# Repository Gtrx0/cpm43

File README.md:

# CPM43
40% Mechanical keyboard PCB

# [Layout](http://www.keyboard-layout-editor.com/#/gists/e3d0a9a1f7fb6537a82bb3f0c82ddf35)

## Features
* In-switch LED support.
* Individually addressible RGB underglow provided by 14 separate WS2812B LEDs.
* USB Type-C connector on the left side.
* Compatible with Cherry MX and ALPS switches. 
* Integrated 16MHz Atmega32u4 microcontroller for better QMK compatibility.
* USB ESD protection circuit.
* ICSP programming header just in case you try something a bit too extreme and need to unbrick it.
* 0805 SMD and through hole Diode/resistor compatibility for ease of assembly.
* USB breakout for extra redundency.

## Warning
KiCad 5 or above is needed to open this project. KiCad 4 or below won't work.

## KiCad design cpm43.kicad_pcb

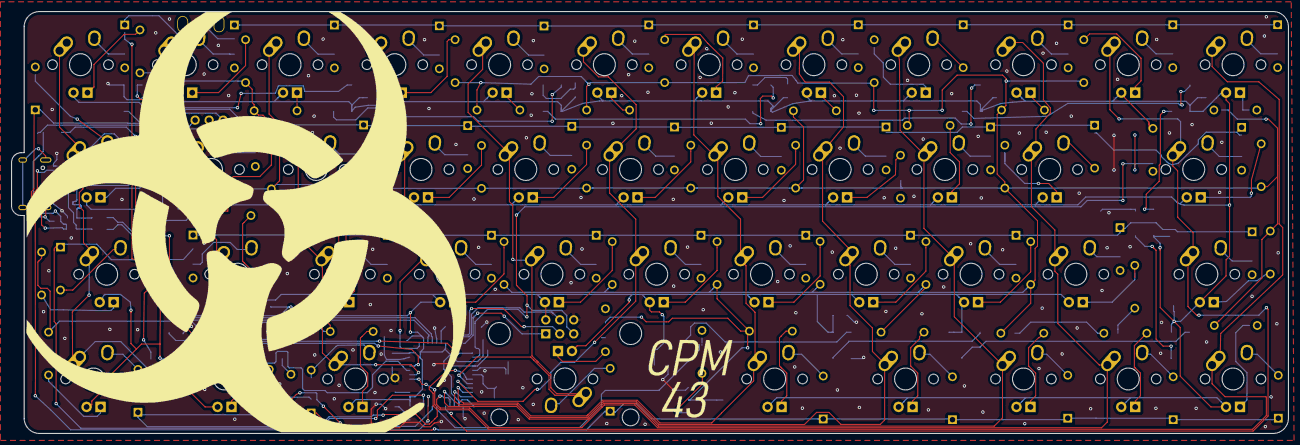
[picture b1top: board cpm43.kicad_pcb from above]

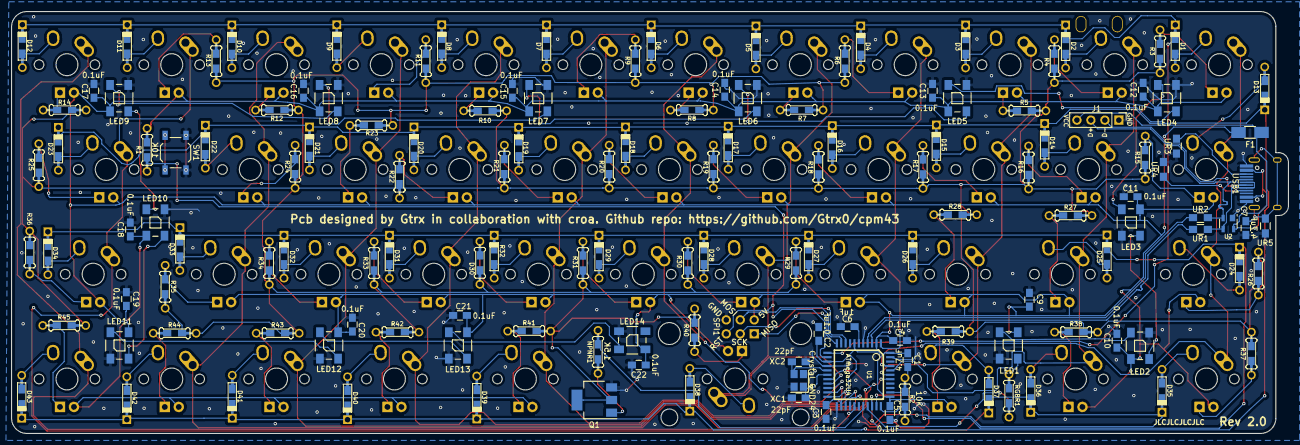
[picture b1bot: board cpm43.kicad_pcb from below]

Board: 2 copper layers, 232.2 x 76.7 mm, 186 parts (50 on the bottom side), 138 nets.

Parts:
C1: 0.1uf; C_0805_HandSoldering
C2, C3, C5, C9, C10, C11, C12, C13, C14, C15, C16, C17, C18, C19, C20, C21, C22: 0.1uF; C_0805_HandSoldering
C4, C7: 4.7uF; C_0805_HandSoldering
C6: 1uF; C_0805_HandSoldering
D1, D2, D3, D4, D5, D6, D7, D8, D9, D10, D11, D12, D13, D14, D15, D16, D17, D18, D19, D20, D21, D22, D23, D24, D25, D26, D27, D28, D29, D30, D31, D32, D33, D34, D35, D36, D37, D38, D39, D40, D41, D42, D43: D; Diode-Hybrid-Back
F1: 500mA Hold; Fuse_SMD1206_HandSoldering
J1: Conn_01x04; Pin_Header_Straight_1x04_Pitch2.54mm
LED1, LED2, LED3, LED4, LED5, LED6, LED7, LED8, LED9, LED10, LED11, LED12, LED13, LED14: WS2812B
MX1, MX2, MX3, MX4, MX5, MX6, MX7, MX8, MX9, MX10, MX11, MX12, MX14, MX15, MX16, MX17, MX18, MX19, MX20, MX21, MX22, MX25, MX26, MX27, MX28, MX29, MX30, MX31, MX32, MX33, MX41, MX42, MX43: MX-1U
MX13: MX-1.25U; MX-1.25U-FLIPPED
MX23: MX-1.75U
MX24: MX-1.5U
MX34: MX-1.25U; MX-1.5U
MX35, MX36, MX37, MX39, MX40: MX-1.25U
MX38: MX-2.75U
NPNR1: 1.5k; Resistor-Hybrid-Back
P?: CONN_1; PIN_1
P?#2: CONN_1; PIN_1
Q1: Q_NPN_BCE; SOT-223-3_TabPin2
R1, R2: 10k; Resistor-Hybrid-Back
R3, R4, R5, R6, R7, R8, R9, R10, R11, R12, R13, R14, R15, R16, R17, R18, R19, R20, R21, R22, R23, R24, R25, R26, R27, R28, R29, R30, R31, R32, R33, R34, R35, R36, R37, R38, R39, R40, R41, R42, R43, R44, R45: 470; Resistor-Hybrid-Back
RGBR1: 470; Resistor-Hybrid-Back
SPI1: 2x3 SPI; Pin_Header_Straight_2x03_Pitch2.54mm
SW1: SW_PUSH; SW_SPST_TL3342
U1: ATmega32U4; QFP44
U2: PRTR5V0U2X; SOT143B
UR1, UR2: 22; R_0805_HandSoldering
UR3, UR4: 5.1k; R_0805_HandSoldering
UR5: 1M; R_0805_HandSoldering
USB1: HRO-TYPE-C-31-M-12; HRO-TYPE-C-31-M-12-HandSoldering
X1: Crystal_GND24; Crystal_SMD_3225-4pin_3.2x2.5mm
XC1, XC2: 22pF; C_0805_HandSoldering

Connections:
+5V: C1.1, C2.1, C3.1, C4.1, C5.1, C9.1, C10.1, C11.1, C12.1, C13.1, C14.1, C15.1, C16.1, C17.1, C18.1, C19.1, C20.1, C21.1, C22.1, F1.2, LED1.1, LED2.1, LED3.1, LED4.1, LED5.1, LED6.1, LED7.1, LED8.1, LED9.1, LED10.1, LED11.1, LED12.1, LED13.1, LED14.1, MX1.3, MX2.3, MX3.3, MX4.3, MX5.3, MX6.3, MX7.3, MX8.3, MX9.3, MX10.3, MX11.3, MX12.3, MX13.3, MX14.3, MX15.3, MX16.3, MX17.3, MX18.3, MX19.3, MX20.3, MX21.3, MX22.3, MX23.3, MX24.3, MX25.3, MX26.3, MX27.3, MX28.3, MX29.3, MX30.3, MX31.3, MX32.3, MX33.3, MX34.3, MX35.3, MX36.3, MX37.3, MX38.3, MX39.3, MX40.3, MX41.3, MX42.3, MX43.3, R1.1, SPI1.2, U1.2, U1.7, U1.14, U1.24, U1.34, U1.44
COL0: MX1.1, MX13.1, MX24.1, MX35.1, U1.41
COL1: MX2.1, MX14.1, MX25.1, MX36.1, U1.40
COL2: MX3.1, MX15.1, MX26.1, MX37.1, U1.39
COL3: MX4.1, MX16.1, MX27.1, U1.1
COL4: MX5.1, MX17.1, MX28.1, MX38.1, U1.19
COL5: MX6.1, MX18.1, MX29.1, U1.20
COL6: MX7.1, MX19.1, MX30.1, MX39.1, U1.21
COL7: MX8.1, MX20.1, MX31.1, MX40.1, U1.22
COL8: MX9.1, MX21.1, MX32.1, MX41.1, U1.25
COL9: MX10.1, MX22.1, MX33.1, MX42.1, U1.26
COL10: MX11.1, MX23.1, MX34.1, U1.27
COL11: MX12.1, MX43.1, U1.38
D+: U1.4, UR2.1
D-: U1.3, UR1.2
GND: C1.2, C2.2, C3.2, C4.2, C5.2, C6.1, C7.1, C9.2, C10.2, C11.2, C12.2, C13.2, C14.2, C15.2, C16.2, C17.2, C18.2, C19.2, C20.2, C21.2, C22.2, J1.1, LED1.3, LED2.3, LED3.3, LED4.3, LED5.3, LED6.3, LED7.3, LED8.3, LED9.3, LED10.3, LED11.3, LED12.3, LED13.3, LED14.3, Q1.3, R2.2, SPI1.6, SW1.1, U1.5, U1.15, U1.23, U1.35, U1.43, U2.1, UR3.1, UR4.2, UR5.1, USB1.1, USB1.12, X1.2, XC1.2, XC2.2
LEDGND: Q1.2, R3.1, R4.1, R5.1, R6.1, R7.1, R8.1, R9.1, R10.1, R11.1, R12.1, R13.1, R14.1, R15.1, R16.1, R17.1, R18.1, R19.1, R20.1, R21.1, R22.1, R23.1, R24.1, R25.1, R26.1, R27.1, R28.1, R29.1, R30.1, R31.1, R32.1, R33.1, R34.1, R35.1, R36.1, R37.1, R38.1, R39.1, R40.1, R41.1, R42.1, R43.1, R44.1, R45.1
LEDPWM: NPNR1.1, U1.29
MISO: SPI1.1, U1.11
MOSI: SPI1.4, U1.10
unnamed: C6.2, U1.6
unnamed: C7.2, UR5.2, USB1.13
unnamed: D1.2, MX1.2
unnamed: D2.2, MX2.2
unnamed: D3.2, MX3.2
unnamed: D4.2, MX4.2
unnamed: D5.2, MX5.2
unnamed: D6.2, MX6.2
unnamed: D7.2, MX7.2
unnamed: D8.2, MX8.2
unnamed: D9.2, MX9.2
unnamed: D10.2, MX10.2
unnamed: D11.2, MX11.2
unnamed: D12.2, MX12.2
unnamed: D13.2, MX13.2
unnamed: D14.2, MX14.2
unnamed: D15.2, MX15.2
unnamed: D16.2, MX16.2
unnamed: D17.2, MX17.2
unnamed: D18.2, MX18.2
unnamed: D19.2, MX19.2
unnamed: D20.2, MX20.2
unnamed: D21.2, MX21.2
unnamed: D22.2, MX22.2
unnamed: D23.2, MX23.2
unnamed: D24.2, MX24.2
unnamed: D25.2, MX25.2
unnamed: D26.2, MX26.2
unnamed: D27.2, MX27.2
unnamed: D28.2, MX28.2
unnamed: D29.2, MX29.2
unnamed: D30.2, MX30.2
unnamed: D31.2, MX31.2
unnamed: D32.2, MX32.2
unnamed: D33.2, MX33.2
unnamed: D34.2, MX34.2
unnamed: D35.2, MX35.2
unnamed: D36.2, MX36.2
unnamed: D37.2, MX37.2
unnamed: D38.2, MX38.2
unnamed: D39.2, MX39.2
unnamed: D40.2, MX40.2
unnamed: D41.2, MX41.2
unnamed: D42.2, MX42.2
unnamed: D43.2, MX43.2
unnamed: J1.2, U2.3, UR1.1, USB1.5, USB1.7
unnamed: J1.3, U2.2, UR2.2, USB1.6, USB1.8
unnamed: LED1.2, LED2.4
unnamed: LED1.4, RGBR1.2
unnamed: LED2.2, LED3.4
unnamed: LED3.2, LED4.4
unnamed: LED4.2, LED5.4
unnamed: LED5.2, LED6.4
unnamed: LED6.2, LED7.4
unnamed: LED7.2, LED8.4
unnamed: LED8.2, LED9.4
unnamed: LED10.2, LED11.4
unnamed: LED9.2, LED10.4
unnamed: LED11.2, LED12.4
unnamed: LED12.2, LED13.4
unnamed: LED13.2, LED14.4
unnamed: MX1.4, R3.2
unnamed: MX2.4, R4.2
unnamed: MX3.4, R5.2
unnamed: MX4.4, R6.2
unnamed: MX5.4, R7.2
unnamed: MX6.4, R8.2
unnamed: MX7.4, R9.2
unnamed: MX8.4, R10.2
unnamed: MX9.4, R11.2
unnamed: MX10.4, R12.2
unnamed: MX11.4, R13.2
unnamed: MX12.4, R14.2
unnamed: MX13.4, R15.2
unnamed: MX14.4, R16.2
unnamed: MX15.4, R17.2
unnamed: MX16.4, R18.2
unnamed: MX17.4, R19.2
unnamed: MX18.4, R20.2
unnamed: MX19.4, R21.2
unnamed: MX20.4, R22.2
unnamed: MX21.4, R23.2
unnamed: MX22.4, R24.2
unnamed: MX23.4, R25.2
unnamed: MX24.4, R26.2
unnamed: MX25.4, R27.2
unnamed: MX26.4, R28.2
unnamed: MX27.4, R29.2
unnamed: MX28.4, R30.2
unnamed: MX29.4, R31.2
unnamed: MX30.4, R32.2
unnamed: MX31.4, R33.2
unnamed: MX32.4, R34.2
unnamed: MX33.4, R35.2
unnamed: MX34.4, R36.2
unnamed: MX35.4, R37.2
unnamed: MX36.4, R38.2
unnamed: MX37.4, R39.2
unnamed: MX38.4, R40.2
unnamed: MX39.4, R41.2
unnamed: MX40.4, R42.2
unnamed: MX41.4, R43.2
unnamed: MX42.4, R44.2
unnamed: MX43.4, R45.2
unnamed: NPNR1.2, Q1.1
unnamed: R2.1, U1.33
unnamed: U1.16, X1.3, XC2.1
unnamed: U1.17, X1.1, XC1.1
unnamed: UR3.2, USB1.10
unnamed: UR4.1, USB1.4
RGBIN: RGBR1.1, U1.30
ROW0: D1.1, D2.1, D3.1, D4.1, D5.1, D6.1, D7.1, D8.1, D9.1, D10.1, D11.1, D12.1, U1.12
ROW1: D13.1, D14.1, D15.1, D16.1, D17.1, D18.1, D19.1, D20.1, D21.1, D22.1, D23.1, U1.31
ROW2: D24.1, D25.1, D26.1, D27.1, D28.1, D29.1, D30.1, D31.1, D32.1, D33.1, D34.1, U1.32
ROW3: D35.1, D36.1, D37.1, D38.1, D39.1, D40.1, D41.1, D42.1, D43.1, U1.18
RST: R1.2, SPI1.5, SW1.2, U1.13
SCK: SPI1.3, U1.9
VCC: F1.1, J1.4, U2.4, USB1.2, USB1.11

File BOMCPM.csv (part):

"Source:","C:\Users\Gtrx\Desktop\40%\cpm43.sch"
"Date:","7/16/2018 1:50:26 AM"
"Tool:","Eeschema (6.0.0-rc1-dev)"
"Generator:","C:\Program Files\KiCad\bin\scripting\plugins/bom_csv_grouped_by_value.py"
"Component Count:","186"

"Individual Components:"

"Item","Qty","Reference(s)","Value","LibPart","Footprint","Datasheet"
"","","C1","0.1uF","device:C_Small","Capacitors_SMD:C_0805_HandSoldering",""
"","","C2","0.1uF","device:C_Small","Capacitors_SMD:C_0805_HandSoldering",""
"","","C3","0.1uF","device:C_Small","Capacitors_SMD:C_0805_HandSoldering",""
"","","C4","4.7uF","device:C_Small","Capacitors_SMD:C_0805_HandSoldering",""
"","","C5","0.1uF","device:C_Small","Capacitors_SMD:C_0805_HandSoldering",""
"","","C6","1uF","device:C_Small","Capacitors_SMD:C_0805_HandSoldering",""
"","","C7","4.7uF","device:C_Small","Capacitors_SMD:C_0805_HandSoldering",""
"","","C8","0.1uF","device:C_Small","Capacitors_SMD:C_0805_HandSoldering",""
"","","C9","0.1uF","device:C_Small","Capacitors_SMD:C_0805_HandSoldering",""
"","","C10","0.1uF","device:C_Small","Capacitors_SMD:C_0805_HandSoldering",""
"","","C11","0.1uF","device:C_Small","Capacitors_SMD:C_0805_HandSoldering",""
"","","C12","0.1uF","device:C_Small","Capacitors_SMD:C_0805_HandSoldering",""
"","","C13","0.1uF","device:C_Small","Capacitors_SMD:C_0805_HandSoldering",""
"","","C14","0.1uF","device:C_Small","Capacitors_SMD:C_0805_HandSoldering",""
"","","C15","0.1uF","device:C_Small","Capacitors_SMD:C_0805_HandSoldering",""
"","","C16","0.1uF","device:C_Small","Capacitors_SMD:C_0805_HandSoldering",""
"","","C17","0.1uF","device:C_Small","Capacitors_SMD:C_0805_HandSoldering",""
"","","C18","0.1uF","device:C_Small","Capacitors_SMD:C_0805_HandSoldering",""
"","","C19","0.1uF","device:C_Small","Capacitors_SMD:C_0805_HandSoldering",""
"","","C20","0.1uF","device:C_Small","Capacitors_SMD:C_0805_HandSoldering",""
"","","C21","0.1uF","device:C_Small","Capacitors_SMD:C_0805_HandSoldering",""
"","","C22","0.1uF","device:C_Small","Capacitors_SMD:C_0805_HandSoldering",""
"","","C23","0.1uF","device:C_Small","Capacitors_SMD:C_0805_HandSoldering",""
"","","D1","D","device:D_ALT","Keebio-Parts:Diode-Hybrid-Back",""
"","","D2","D","device:D_ALT","Keebio-Parts:Diode-Hybrid-Back",""
"","","D3","D","device:D_ALT","Keebio-Parts:Diode-Hybrid-Back",""
"","","D4","D","device:D_ALT","Keebio-Parts:Diode-Hybrid-Back",""
"","","D5","D","device:D_ALT","Keebio-Parts:Diode-Hybrid-Back",""
"","","D6","D","device:D_ALT","Keebio-Parts:Diode-Hybrid-Back",""
"","","D7","D","device:D_ALT","Keebio-Parts:Diode-Hybrid-Back",""
"","","D8","D","device:D_ALT","Keebio-Parts:Diode-Hybrid-Back",""
"","","D9","D","device:D_ALT","Keebio-Parts:Diode-Hybrid-Back",""
"","","D10","D","device:D_ALT","Keebio-Parts:Diode-Hybrid-Back",""
"","","D11","D","device:D_ALT","Keebio-Parts:Diode-Hybrid-Back",""
"","","D12","D","device:D_ALT","Keebio-Parts:Diode-Hybrid-Back",""
"","","D13","D","device:D_ALT","Keebio-Parts:Diode-Hybrid-Back",""
"","","D14","D","device:D_ALT","Keebio-Parts:Diode-Hybrid-Back",""
"","","D15","D","device:D_ALT","Keebio-Parts:Diode-Hybrid-Back",""
"","","D16","D","device:D_ALT","Keebio-Parts:Diode-Hybrid-Back",""
"","","D17","D","device:D_ALT","Keebio-Parts:Diode-Hybrid-Back",""
"","","D18","D","device:D_ALT","Keebio-Parts:Diode-Hybrid-Back",""
"","","D19","D","device:D_ALT","Keebio-Parts:Diode-Hybrid-Back",""
"","","D20","D","device:D_ALT","Keebio-Parts:Diode-Hybrid-Back",""
"","","D21","D","device:D_ALT","Keebio-Parts:Diode-Hybrid-Back",""
"","","D22","D","device:D_ALT","Keebio-Parts:Diode-Hybrid-Back",""
"","","D23","D","device:D_ALT","Keebio-Parts:Diode-Hybrid-Back",""
"","","D24","D","device:D_ALT","Keebio-Parts:Diode-Hybrid-Back",""
"","","D25","D","device:D_ALT","Keebio-Parts:Diode-Hybrid-Back",""
"","","D26","D","device:D_ALT","Keebio-Parts:Diode-Hybrid-Back",""
"","","D27","D","device:D_ALT","Keebio-Parts:Diode-Hybrid-Back",""
"","","D28","D","device:D_ALT","Keebio-Parts:Diode-Hybrid-Back",""
"","","D29","D","device:D_ALT","Keebio-Parts:Diode-Hybrid-Back",""
"","","D30","D","device:D_ALT","Keebio-Parts:Diode-Hybrid-Back",""
"","","D31","D","device:D_ALT","Keebio-Parts:Diode-Hybrid-Back",""
"","","D32","D","device:D_ALT","Keebio-Parts:Diode-Hybrid-Back",""
"","","D33","D","device:D_ALT","Keebio-Parts:Diode-Hybrid-Back",""
"","","D34","D","device:D_ALT","Keebio-Parts:Diode-Hybrid-Back",""
"","","D35","D","device:D_ALT","Keebio-Parts:Diode-Hybrid-Back",""
"","","D36","D","device:D_ALT","Keebio-Parts:Diode-Hybrid-Back",""
"","","D37","D","device:D_ALT","Keebio-Parts:Diode-Hybrid-Back",""
"","","D38","D","device:D_ALT","Keebio-Parts:Diode-Hybrid-Back",""
"","","D39","D","device:D_ALT","Keebio-Parts:Diode-Hybrid-Back",""
"","","D40","D","device:D_ALT","Keebio-Parts:Diode-Hybrid-Back",""
"","","D41","D","device:D_ALT","Keebio-Parts:Diode-Hybrid-Back",""
"","","D42","D","device:D_ALT","Keebio-Parts:Diode-Hybrid-Back",""
"","","D43","D","device:D_ALT","Keebio-Parts:Diode-Hybrid-Back",""
"","","F1","500mA Hold","device:Polyfuse_Small","Keebio-Parts:Diode-Hybrid-Back",""
"","","LED1","WS2812B","ws2812b:WS2812B","WS2812B:WS2812B",""
"","","LED2","WS2812B","ws2812b:WS2812B","WS2812B:WS2812B",""
"","","LED3","WS2812B","ws2812b:WS2812B","WS2812B:WS2812B",""
"","","LED4","WS2812B","ws2812b:WS2812B","WS2812B:WS2812B",""
"","","LED5","WS2812B","ws2812b:WS2812B","WS2812B:WS2812B",""
"","","LED6","WS2812B","ws2812b:WS2812B","WS2812B:WS2812B",""
"","","LED7","WS2812B","ws2812b:WS2812B","WS2812B:WS2812B",""
"","","LED8","WS2812B","ws2812b:WS2812B","WS2812B:WS2812B",""
"","","LED9","WS2812B","ws2812b:WS2812B","WS2812B:WS2812B",""
"","","LED10","WS2812B","ws2812b:WS2812B","WS2812B:WS2812B",""
"","","LED11","WS2812B","ws2812b:WS2812B","WS2812B:WS2812B",""
"","","LED12","WS2812B","ws2812b:WS2812B","WS2812B:WS2812B",""
"","","LED13","WS2812B","ws2812b:WS2812B","WS2812B:WS2812B",""
"","","LED14","WS2812B","ws2812b:WS2812B","WS2812B:WS2812B",""
"","","LED15","WS2812B","ws2812b:WS2812B","WS2812B:WS2812B",""
"","","MX1","MX-1U","MX_Alps_Hybrids:MX-1U","MX_Alps_Hybrid:MX-1U-NoLED",""
"","","MX2","MX-1U","MX_Alps_Hybrids:MX-1U","MX_Alps_Hybrid:MX-1U-NoLED",""
"","","MX3","MX-1U","MX_Alps_Hybrids:MX-1U","MX_Alps_Hybrid:MX-1U-NoLED",""
"","","MX4","MX-1U","MX_Alps_Hybrids:MX-1U","MX_Alps_Hybrid:MX-1U-NoLED",""
"","","MX5","MX-1U","MX_Alps_Hybrids:MX-1U","MX_Alps_Hybrid:MX-1U-NoLED",""
"","","MX6","MX-1U","MX_Alps_Hybrids:MX-1U","MX_Alps_Hybrid:MX-1U-NoLED",""
"","","MX7","MX-1U","MX_Alps_Hybrids:MX-1U","MX_Alps_Hybrid:MX-1U-NoLED",""
"","","MX8","MX-1U","MX_Alps_Hybrids:MX-1U","MX_Alps_Hybrid:MX-1U-NoLED",""
"","","MX9","MX-1U","MX_Alps_Hybrids:MX-1U","MX_Alps_Hybrid:MX-1U-NoLED",""
"","","MX10","MX-1U","MX_Alps_Hybrids:MX-1U","MX_Alps_Hybrid:MX-1U-NoLED",""
"","","MX11","MX-1U","MX_Alps_Hybrids:MX-1U","MX_Alps_Hybrid:MX-1U-NoLED",""
"","","MX12","MX-1U","MX_Alps_Hybrids:MX-1U","MX_Alps_Hybrid:MX-1U-NoLED",""
"","","MX13","MX-1.25U","MX_Alps_Hybrids:MX-1.25U","MX_Alps_Hybrid:MX-1.25U",""
"","","MX14","MX-1U","MX_Alps_Hybrids:MX-1U","MX_Alps_Hybrid:MX-1U",""
"","","MX15","MX-1U","MX_Alps_Hybrids:MX-1U","MX_Alps_Hybrid:MX-1U",""
"","","MX16","MX-1U","MX_Alps_Hybrids:MX-1U","MX_Alps_Hybrid:MX-1U",""
"","","MX17","MX-1U","MX_Alps_Hybrids:MX-1U","MX_Alps_Hybrid:MX-1U",""
"","","MX18","MX-1U","MX_Alps_Hybrids:MX-1U","MX_Alps_Hybrid:MX-1U",""
"","","MX19","MX-1U","MX_Alps_Hybrids:MX-1U","MX_Alps_Hybrid:MX-1U",""
"","","MX20","MX-1U","MX_Alps_Hybrids:MX-1U","MX_Alps_Hybrid:MX-1U",""
"","","MX21","MX-1U","MX_Alps_Hybrids:MX-1U","MX_Alps_Hybrid:MX-1U",""
"","","MX22","MX-1U","MX_Alps_Hybrids:MX-1U","MX_Alps_Hybrid:MX-1U",""
"","","MX23","MX-1.75U","MX_Alps_Hybrids:MX-1.75U","MX_Alps_Hybrid:MX-1.75U",""
"","","MX24","MX-1.5U","MX_Alps_Hybrids:MX-1.5U","MX_Alps_Hybrid:MX-1.5U",""
"","","MX25","MX-1U","MX_Alps_Hybrids:MX-1U","MX_Alps_Hybrid:MX-1U",""
"","","MX26","MX-1U","MX_Alps_Hybrids:MX-1U","MX_Alps_Hybrid:MX-1U",""
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
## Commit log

2018-07-20 Kicad Project Files
    Designed in kicad 5. Wont work in kicad 4.
2018-07-20 Changed BOM and KiCad Files
2018-07-20 Changed renders
2018-07-20 Silkscreen changed
2018-07-21 Edge cut changed, new renders
2018-07-21 Renders Changed
2018-07-21 Added Gerbers
2018-07-23 Edge cuts have been changed
2018-07-26 Changed BOM
2018-07-26 BOM change
2018-07-30 Hand soldering made not so hellish
2018-08-06 Changed decoupling cap value
2018-08-06 BOM changed
2018-08-06 Fixed stab holes
2018-08-09 Changed the switch so that it doesn't pull the reset line low forever
2018-08-10 Bigger ICSP header
2018-08-20 New gerbers and Silkscreen changes
2018-08-30 Tact switch
2018-08-30 Added usb breakout header
2018-08-30 Mounting holes added
2018-09-08 Fixed BS
